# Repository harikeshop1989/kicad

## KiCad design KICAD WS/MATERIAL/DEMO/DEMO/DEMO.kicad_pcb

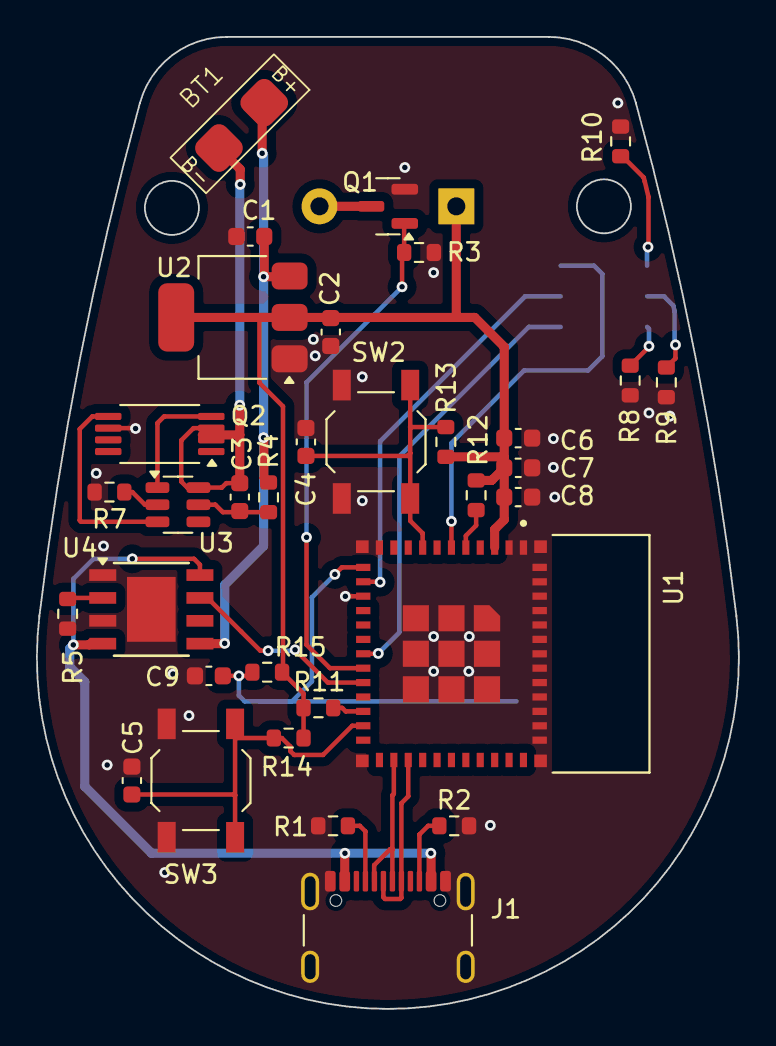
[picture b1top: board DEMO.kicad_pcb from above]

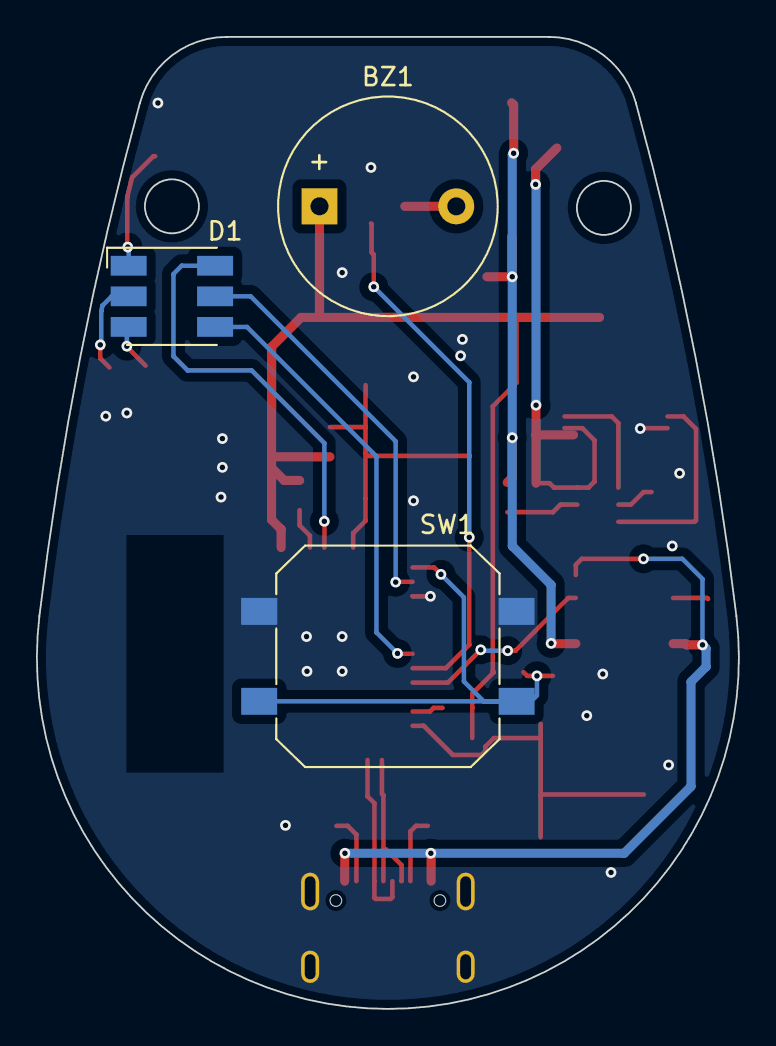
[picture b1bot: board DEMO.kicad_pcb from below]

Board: 2 copper layers, 39.0 x 54.0 mm, 36 parts (3 on the bottom side), 28 nets.

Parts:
BT1: Battery_Cell; LiPoBatt_WLY902030
BZ1: Buzzer; Buzzer_12x9.5RM7.6
C1, C2, C3, C8: 10uF; C_0603_1608Metric
C4, C5, C6, C7, C9: 100nF; C_0603_1608Metric
D1: LED_RGB; LED_RGB_5050-6
J1: USB_C_Receptacle_USB2.0_16P; USB_C_Receptacle_GCT_USB4105-xx-A_16P_TopMnt_Horizontal
Q1: BC847; SOT-23
Q2: FS8205A; TSSOP-8_4.4x3mm_P0.65mm
R1, R2: 5k1; R_0603_1608Metric
R3: 100k; R_0603_1608Metric
R4: 100; R_0603_1608Metric
R5, R8, R9: 1k2; R_0603_1608Metric
R7: 1k; R_0603_1608Metric
R10: 2k2; R_0603_1608Metric
R11, R12, R13, R14, R15: 10k; R_0603_1608Metric
SW1: SW_Push; SW_Push_1P1T_NO_CK_PTS125Sx43PSMTR
SW2, SW3: SW_Push; SW_SPST_TL3342
U1: ESP32-C3-MINI-1-N4
U2: AMS1117-3.3; SOT-223-3_TabPin2
U3: DW01-A; SOT-23-6
U4: TP4056; Diodes_PSOP-8

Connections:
+3V3: BZ1.1 (+), C2.1, C6.1, C7.1, C8.1, R11.1, R12.1, R13.1, R14.1, R15.1, U1.3 (3V3), U2.2 (VO)
+BATT: BT1.1 (+), C1.1, R4.1, U2.3 (VI), U4.5 (BAT)
BOOT: C5.1, R14.2, SW3.2, U1.23 (IO9)
Bulb_1: D1.6 (RA), U1.6 (IO3)
Bulb_2: D1.5 (GA), U1.13 (IO1)
Bulb_3: D1.4 (BA), U1.18 (IO4)
Button: C9.1, R15.2, SW1.2, U1.12 (IO0)
Buzzer: Q1.1 (B), R3.1, U1.19 (IO5)
CHG: U1.20 (IO6), U4.7 (~CHRG)
GND: C1.2, C2.2, C4.2, C5.2, C6.2, C7.2, C8.2, C9.2, J1.A1 (GND), J1.A12 (GND), J1.B1 (GND), J1.B12 (GND), J1.S1 (SHIELD), Q1.2 (E), Q2.6 (S_{2}), R1.2, R2.2, R3.2, R5.1, R7.2, R8.2, R9.2, R10.2, SW1.1, SW2.1, SW3.1, U1.1 (GND), U1.2 (GND), U1.11 (GND), U1.14 (GND), U1.36 (GND), U1.37 (GND), U1.38 (GND), U1.39 (GND), U1.40 (GND), U1.41 (GND), U1.42 (GND), U1.43 (GND), U1.44 (GND), U1.45 (GND), U1.46 (GND), U1.47 (GND), U1.48 (GND), U1.49 (GND), U1.50 (GND), U1.51 (GND), U1.52 (GND), U1.53 (GND), U2.1 (GND), U4.1 (TEMP), U4.3 (GND), U4.9 (EP)
unnamed: BT1.2 (-), C3.2, Q2.2 (S_{1}), Q2.3 (S_{1}), U3.6 (GND)
unnamed: BZ1.2 (-), Q1.3 (C)
unnamed: D1.3 (BK), R8.1
unnamed: D1.2 (GK), R9.1
unnamed: D1.1 (RK), R10.1
unnamed: J1.A5 (CC1), R1.1
unnamed: J1.B5 (CC2), R2.1
unnamed: Q2.4 (G_{1}), U3.1 (OD)
unnamed: Q2.5 (G_{2}), U3.3 (OC)
unnamed: R12.2, U1.5 (IO2)
unnamed: R11.2, U1.22 (IO8)
unnamed: R7.1, U3.2 (CS)
unnamed: C3.1, R4.2, U3.5 (VCC)
unnamed: R5.2, U4.2 (PROG)
RESET: C4.1, R13.2, SW2.2, U1.8 (EN)
USB_DN: J1.A7 (D-), J1.B7 (D-), U1.26 (USB_DN/IO18)
USB_DP: J1.A6 (D+), J1.B6 (D+), U1.27 (USB_DP/IO19)
VBUS: J1.A4 (VBUS), J1.A9 (VBUS), J1.B4 (VBUS), J1.B9 (VBUS), U4.4 (VCC), U4.8 (CE)

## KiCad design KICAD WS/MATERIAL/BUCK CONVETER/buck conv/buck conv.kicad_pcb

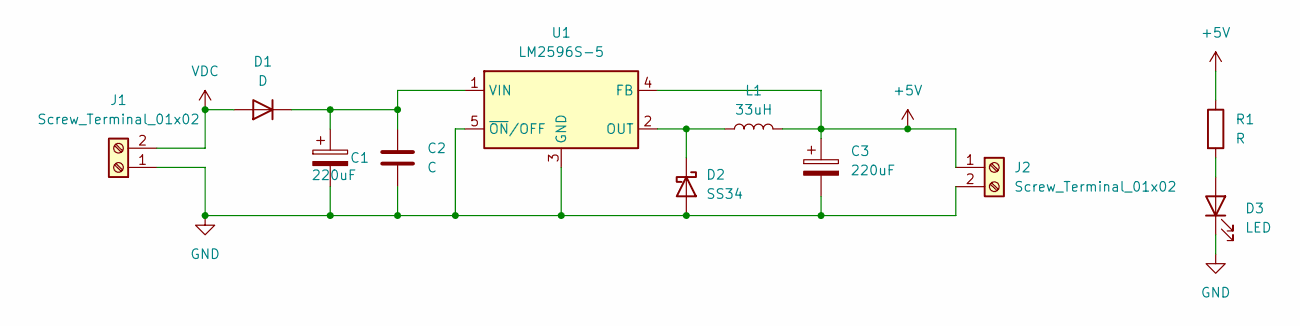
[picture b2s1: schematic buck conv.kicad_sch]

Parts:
C1, C3: 220uF; CP_Elec_8x10
C2: C; C_0603_1608Metric_Pad1.08x0.95mm_HandSolder
D1: D; D_2114_3652Metric
D2: SS34; D_SMA
D3: LED; LED_0402_1005Metric
J1, J2: Screw_Terminal_01x02; TerminalBlock_Phoenix_MKDS-1,5-2-5.08_1x02_P5.08mm_Horizont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
L1: 33uH; L_12x12mm_H4.5mm
R1: R; R_0603_1608Metric
U1: LM2596S-5; TO-263-5_TabPin3

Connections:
+5V: C3.1, J2.1, L1.2, R1.1, U1.4 (FB)
+VDC: C1.1, C2.1, D1.1 (K), U1.1 (VIN)
GND: C1.2, C2.2, C3.2, D2.2 (A), D3.1 (K), J1.1, J2.2, U1.3 (GND), U1.5 (~ON/OFF)
unnamed: D1.2 (A), J1.2
unnamed: D2.1 (K), L1.1, U1.2 (OUT)
unnamed: D3.2 (A), R1.2

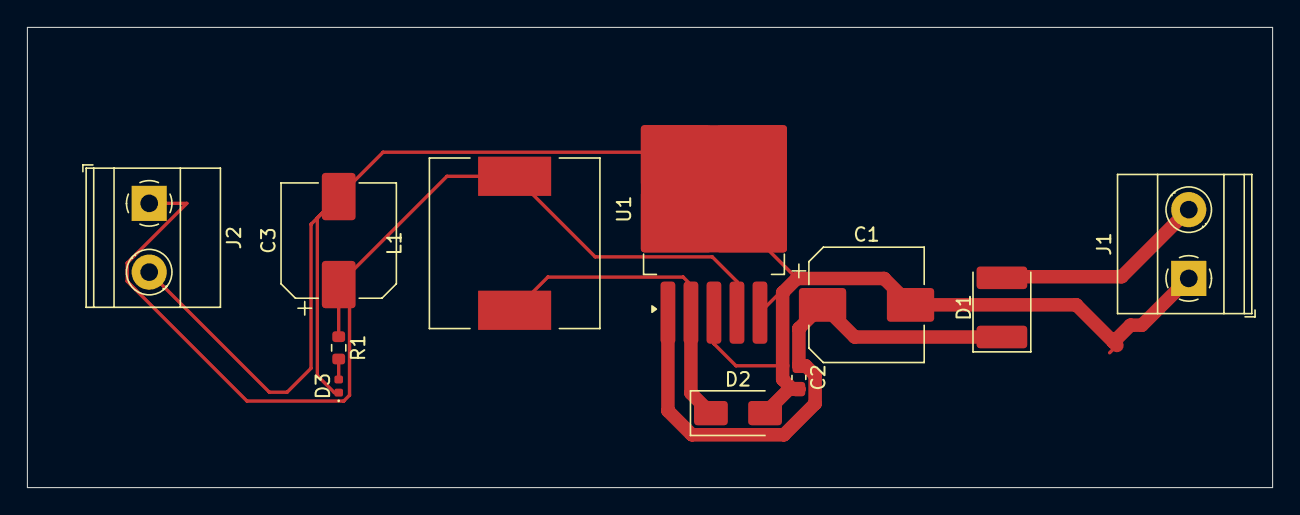
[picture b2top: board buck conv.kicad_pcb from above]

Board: 2 copper layers, 92.0 x 34.0 mm, 11 parts (0 on the bottom side), 6 nets.

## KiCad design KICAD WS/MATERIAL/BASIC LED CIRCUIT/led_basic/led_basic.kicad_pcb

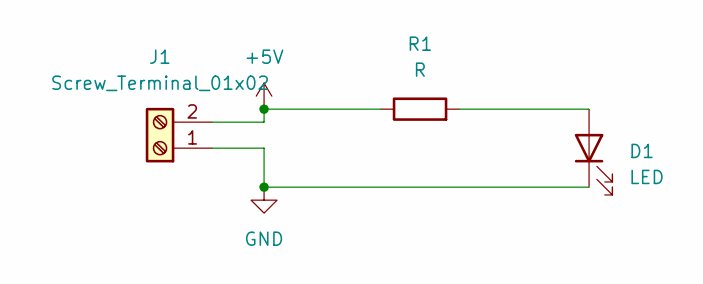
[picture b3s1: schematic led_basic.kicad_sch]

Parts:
D1: LED; LED_D3.0mm
J1: Screw_Terminal_01x02; TerminalBlock_Phoenix_MKDS-1,5-2-5.08_1x02_P5.08mm_Horizont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
R1: R; R_Axial_DIN0204_L3.6mm_D1.6mm_P5.08mm_Horizontal

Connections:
+5V: J1.2, R1.1
GND: D1.1 (K), J1.1
unnamed: D1.2 (A), R1.2

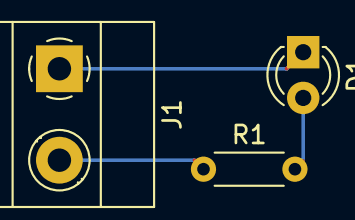
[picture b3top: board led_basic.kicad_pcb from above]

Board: 2 copper layers, 3 parts (0 on the bottom side), 3 nets.

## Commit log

2024-09-12 added all files
